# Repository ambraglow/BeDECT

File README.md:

# BeDect
DECT expansion board for [beepis](https://gitlab.com/linalinn/bepis)

## TODO:
- Add buttons
- figure out speaker vs separate jack vs combo

### sources/materials
[SC14CVMDECT datasheet](https://www.digikey.com/en/htmldatasheets/production/2361758/0/0/1/sc14cvmdect-sf-datasheet.html)
[Redected wiki](https://wiki.redected.org/)
[Open source devboard](https://github.com/funkeleinhorn/sc14cvmdect-devboard)

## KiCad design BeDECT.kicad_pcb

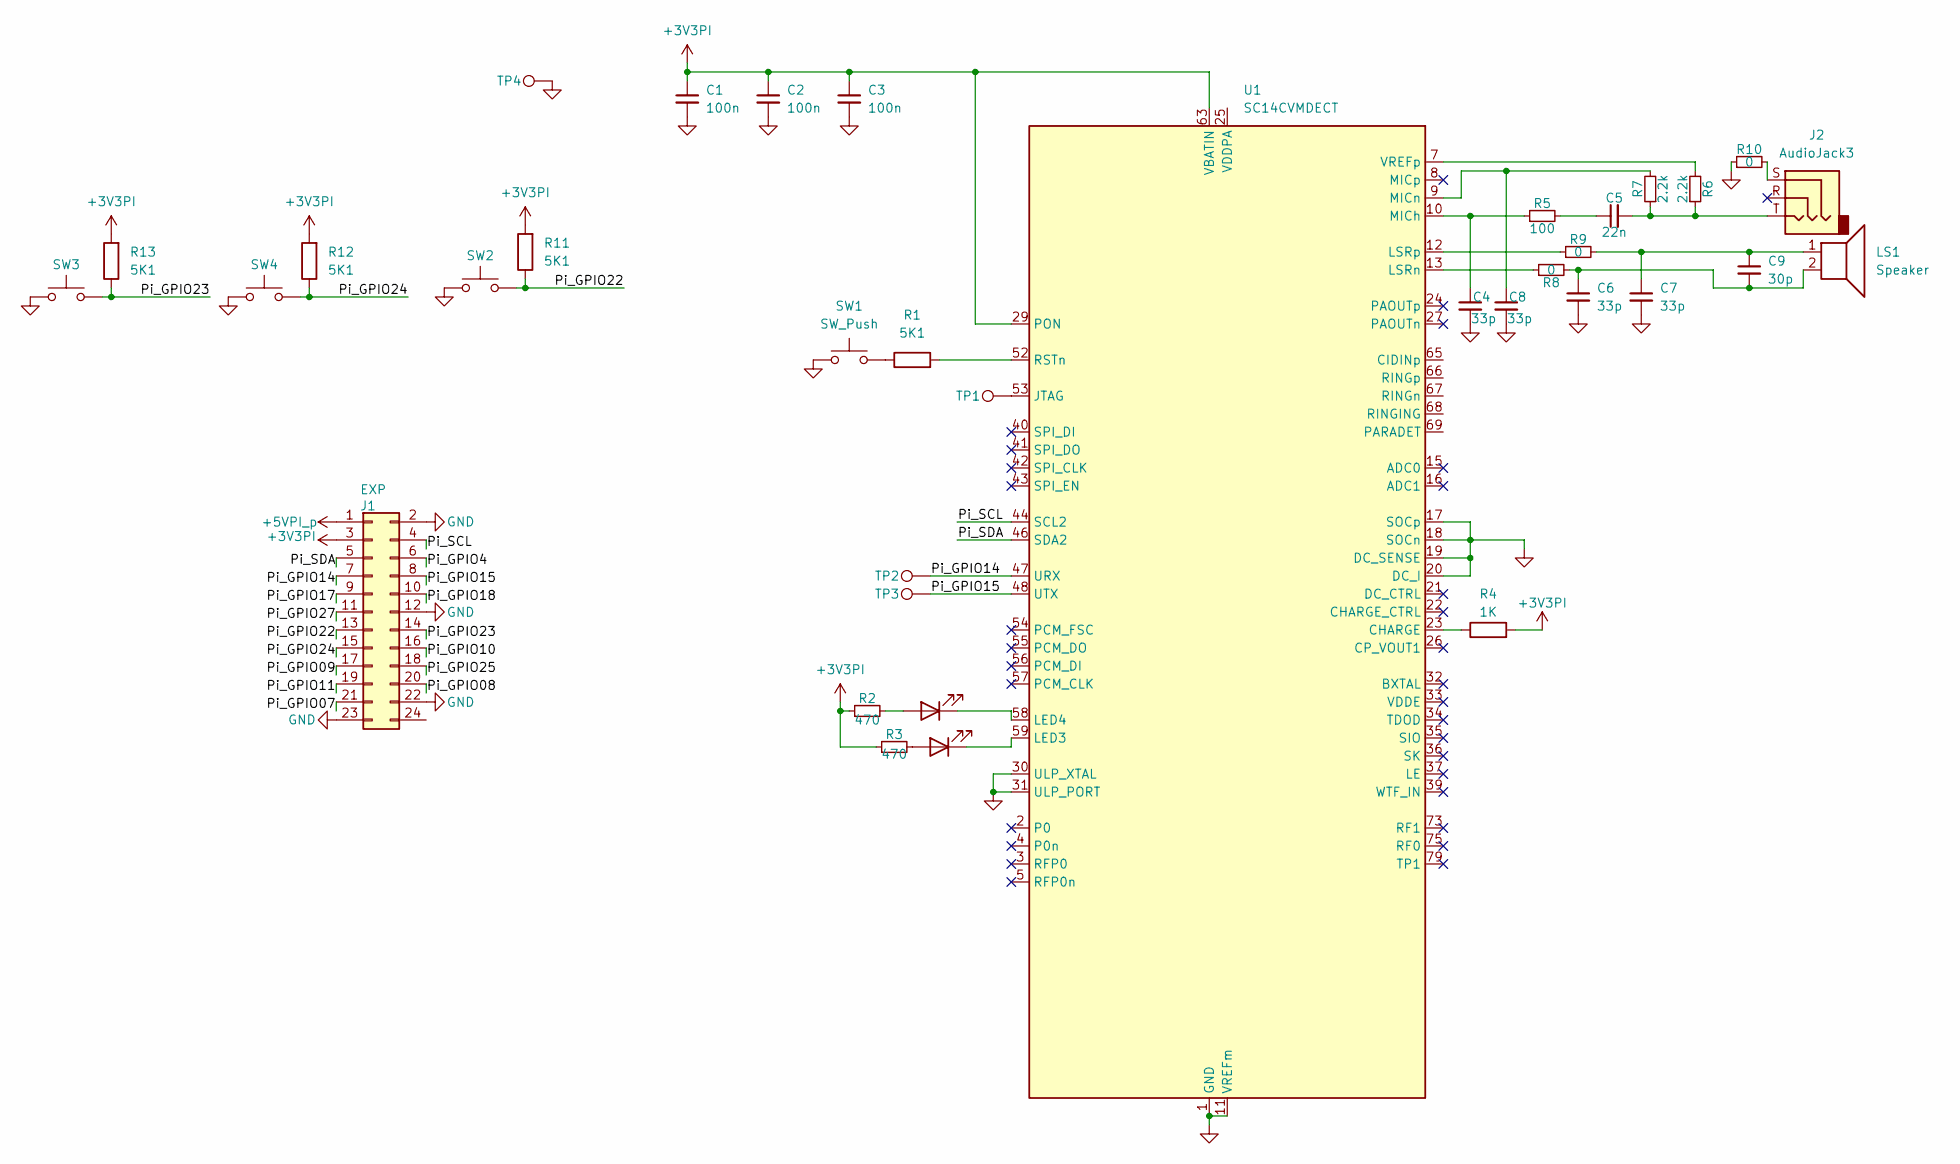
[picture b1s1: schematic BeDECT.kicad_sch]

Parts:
C1, C2, C3: 100n; C_0603_1608Metric
C4, C6, C7, C8: 33p; C_0603_1608Metric
C5: 22n; C_0603_1608Metric
C9: 30p; C_0603_1608Metric
D1, D2: LED; LED_0603_1608Metric
J1: EXP; BepisAddon_v1
J2: AudioJack3; Jack_3.5mm_Lumberg_1503_02_Horizontal
LS1: Speaker; PinHeader_1x02_P2.54mm_Vertical
R1, R11, R12, R13: 5K1; R_0603_1608Metric
R2, R3: 470; R_0603_1608Metric
R4: 1K; R_0603_1608Metric
R5: 100; R_0603_1608Metric
R6, R7: 2.2k; R_0603_1608Metric
R8, R9, R10: 0; R_0603_1608Metric
SW1: SW_Push; SW_SPST_PTS647_Sx70
SW2, SW3, SW4: SW_Push; 1TS003A-1800-3500A-CT
TP1, TP2, TP3: TestPoint; TestPoint_Pad_D2.0mm
TP4: TestPoint; TestPoint_Pad_D1.0mm
U1: SC14CVMDECT

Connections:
+3V3PI: C1.1, C2.1, C3.1, J1.3, R2.1, R3.1, R4.2, R11.2, R12.2, R13.2, U1.29 (PON), U1.63 (VBATIN), U1.64 (VBATIN)
+5VPI_p: J1.1
/Pi_GPIO4: J1.6
/Pi_GPIO07: J1.21
/Pi_GPIO08: J1.20
/Pi_GPIO09: J1.17
/Pi_GPIO10: J1.16
/Pi_GPIO11: J1.19
/Pi_GPIO14: J1.7, TP2.1, U1.47 (URX)
/Pi_GPIO15: J1.8, TP3.1, U1.48 (UTX)
/Pi_GPIO17: J1.9
/Pi_GPIO18: J1.10
/Pi_GPIO22: J1.13, R11.1, SW2.2
/Pi_GPIO23: J1.14, R13.1, SW3.2
/Pi_GPIO24: J1.15, R12.1, SW4.2
/Pi_GPIO25: J1.18
/Pi_GPIO27: J1.11
/Pi_SCL: J1.4, U1.44 (SCL2)
/Pi_SDA: J1.5, U1.46 (SDA2)
GND: C1.2, C2.2, C3.2, C4.2, C6.2, C7.2, C8.2, J1.2, J1.12, J1.22, J1.23, R10.1, SW1.1, SW2.1, SW3.1, SW4.1, TP4.1, U1.1 (GND), U1.6 (GND), U1.11 (VREFm), U1.14 (GND), U1.17 (SOCp), U1.18 (SOCn), U1.19 (DC_SENSE), U1.20 (DC_I), U1.28 (GND), U1.30 (ULP_XTAL), U1.31 (ULP_PORT), U1.38 (GND), U1.45 (GND), U1.49 (GND), U1.50 (GND), U1.51 (GND), U1.60 (GND), U1.70 (GND), U1.71 (GND), U1.72 (GND), U1.74 (GND), U1.76 (GND), U1.77 (GND), U1.78 (GND), U1.80 (GND)
unnamed: C5.1, R5.2
unnamed: C5.2, J2.T, R6.1, R7.1
unnamed: C6.1, C9.2, LS1.2, R8.2
unnamed: C7.1, C9.1, LS1.1, R9.2
unnamed: D1.2 (A), R3.2
unnamed: D1.1 (K), U1.59 (LED3)
unnamed: D2.2 (A), R2.2
unnamed: D2.1 (K), U1.58 (LED4)
unnamed: J2.S, R10.2
unnamed: R1.1, SW1.2
unnamed: R4.1, U1.23 (CHARGE)
unnamed: TP1.1, U1.53 (JTAG)
unnamed: R8.1, U1.13 (LSRn)
unnamed: R9.1, U1.12 (LSRp)
unnamed: C4.1, R5.1, U1.10 (MICh)
unnamed: C8.1, R7.2, U1.9 (MICn)
unnamed: R1.2, U1.52 (RSTn)
unnamed: R6.2, U1.7 (VREFp)

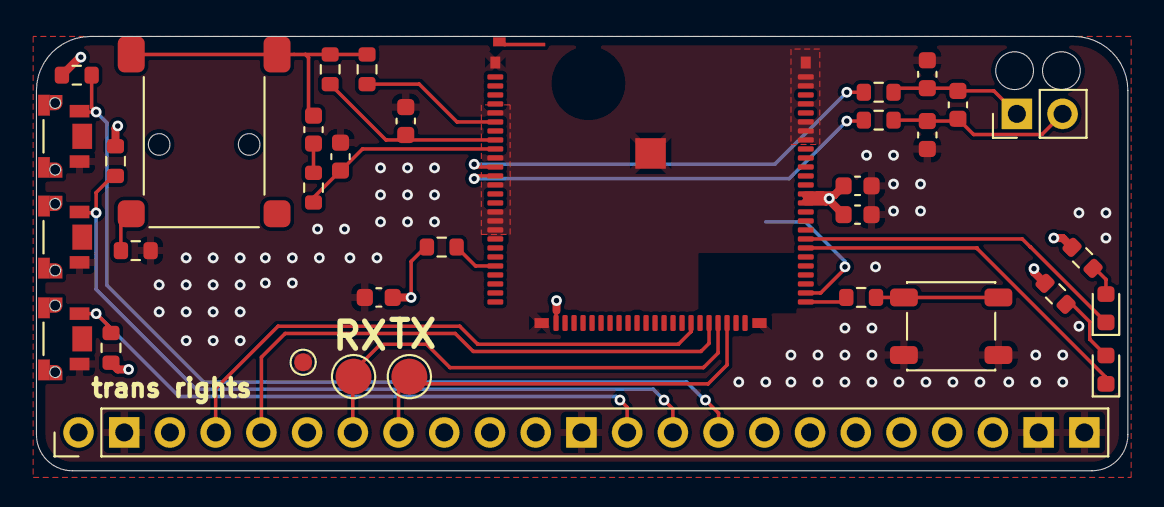
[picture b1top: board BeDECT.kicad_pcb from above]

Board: 4 copper layers, 60.6 x 24.1 mm, 36 parts (1 on the bottom side), 27 nets.

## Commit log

2024-12-30 remove 3d model
2024-12-30 update 3d model
2024-12-30 update PCB
2024-12-30 fix the funny on PCB
2024-12-30 Update PCB: Add button pullups
2024-12-30 Update PCB: via stitching, silkscreen
2024-12-31 Update Schematic: parallel speaker capacitor value
2025-05-07 Create LICENSE
